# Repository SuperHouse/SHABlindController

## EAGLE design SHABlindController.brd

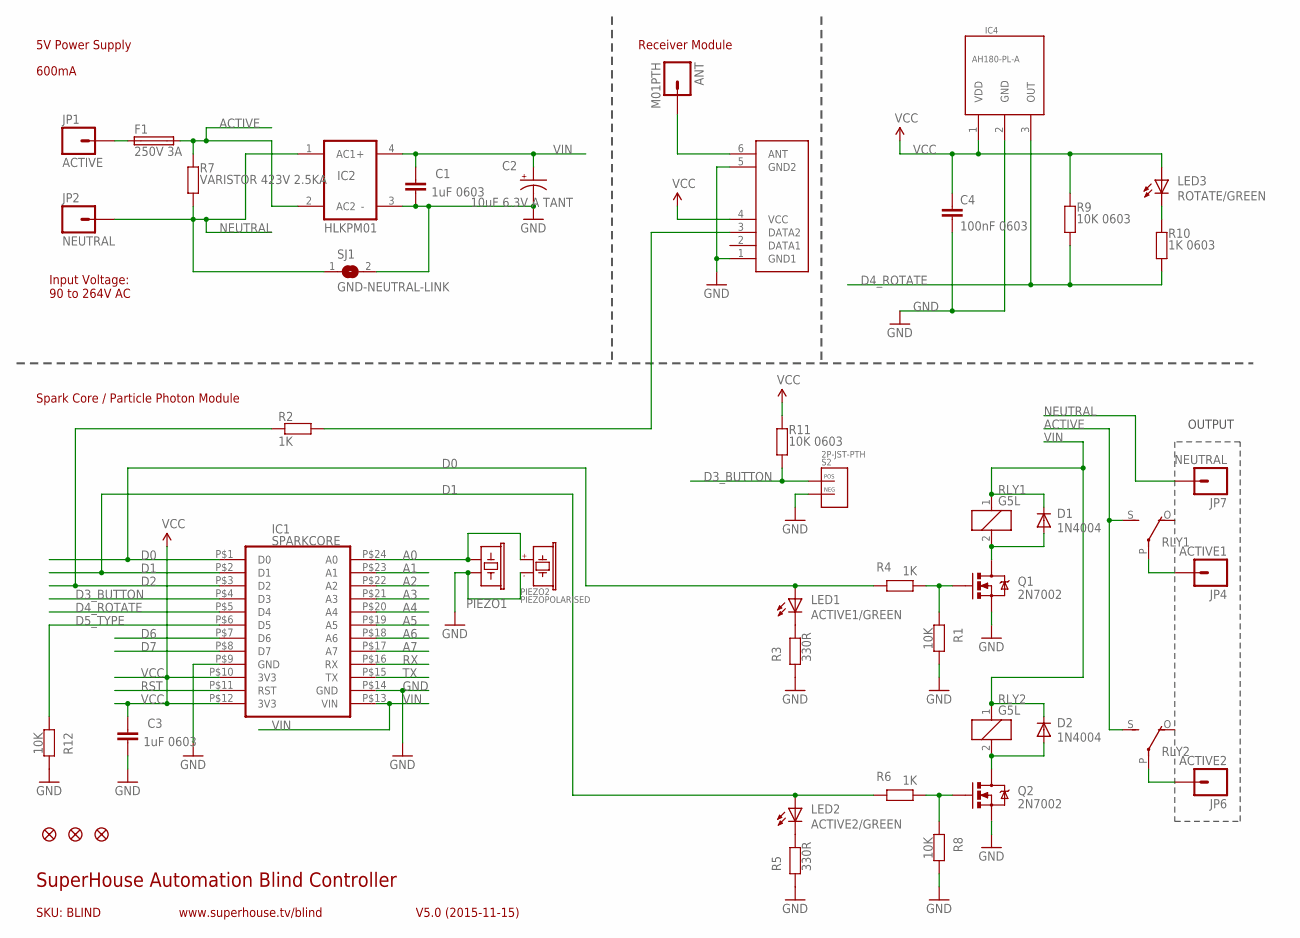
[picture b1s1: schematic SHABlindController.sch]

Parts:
ANT: M01PTH; 1X01
C1, C3: 1uF 0603; 0603@1
C2: 10uF 6.3V A TANT; EIA3216
C4: 100nF 0603; 0603
D1, D2: 1N4004; SMB-DIODE
F1: 250V 3A; PICOFUSE
FID1, FID2, FID3: FIDUCIAL1X2.5; FIDUCIAL-1X2.5
IC1: SPARKCORE
IC2: HLKPM01
IC3: RXB1; RX-B1-SHORT-FLAT
IC4: AH180-PL-A; TO92FLATUP
JP1: ACTIVE; 1X01LARGE
JP2, JP7: NEUTRAL; 1X01LARGE
JP4: ACTIVE1; 1X01LARGE
JP6: ACTIVE2; 1X01LARGE
LED1: ACTIVE1/GREEN; LED-0603
LED2: ACTIVE2/GREEN; LED-0603
LED3: ROTATE/GREEN; LED-0603
PIEZO1: BUZZERSMD12X12; BUZZER-12X12-SMT
PIEZO2: PIEZOPOLARISED; PIEZO12MMWIDEPOLARISED
Q1, Q2: 2N7002; SOT23-3
R1, R8, R12: 10K; 0603
R2, R4, R6: 1K; 0603
R3, R5: 330R; 0603
R7: VARISTOR 423V 2.5KA; AXIAL-0.3
R9, R11: 10K 0603; 0603
R10: 1K 0603; 0603
RLY1, RLY2: G5L; G5LE
S2: 2P-JST-PTH; JST-2MM-TH-RA
SJ1: GND-NEUTRAL-LINK; SJ

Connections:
A0: IC1.P$24 (A0), PIEZO1.1, PIEZO2.1 (+)
A1: IC1.P$23 (A1)
A2: IC1.P$22 (A2)
A3: IC1.P$21 (A3)
A4: IC1.P$20 (A4)
A5: IC1.P$19 (A5)
A6: IC1.P$18 (A6)
A7: IC1.P$17 (A7)
ACTIVE: F1.2, IC2.2 (AC2), R7.P$2 (2), RLY1.S, RLY2.S
D0: IC1.P$1 (D0), LED1.A, R4.2
D1: IC1.P$2 (D1), LED2.A, R6.2
D2: IC1.P$3 (D2), R2.1
D3_BUTTON: IC1.P$4 (D3), R11.1, S2.POS
D4_ROTATE: IC1.P$5 (D4), IC4.3 (OUT), R9.1, R10.2
D5_TYPE: IC1.P$6 (D5), R12.1
D6: IC1.P$7 (D6)
D7: IC1.P$8 (D7)
GND: C1.2, C2.C (-), C3.2, C4.2, IC1.P$9 (GND), IC1.P$14 (GND), IC2.3 (-), IC3.1 (GND1), IC3.5 (GND2), IC4.2 (GND), PIEZO1.2, PIEZO2.2 (-), Q1.2 (S), Q2.2 (S), R1.2, R3.1, R5.1, R8.2, R12.2, S2.NEG, SJ1.2
unnamed: ANT.1, IC3.6 (ANT)
unnamed: LED2.C, R5.2
unnamed: D2.A, Q2.3 (D), RLY2.2
unnamed: D1.A, Q1.3 (D), RLY1.2
unnamed: Q1.1 (G), R1.1, R4.1
unnamed: Q2.1 (G), R6.1, R8.1
unnamed: F1.1, JP1.1
unnamed: LED3.C, R10.1
unnamed: JP4.1, RLY1.P
unnamed: JP6.1, RLY2.P
unnamed: LED1.C, R3.2
unnamed: IC3.3 (DATA2), R2.2
NEUTRAL: IC2.1 (AC1), JP2.1, JP7.1, R7.P$1 (1), SJ1.1
RST: IC1.P$11 (RST)
RX: IC1.P$16 (RX)
TX: IC1.P$15 (TX)
VCC: C3.1, C4.1, IC1.P$10 (3V3), IC1.P$12 (3V3), IC3.4 (VCC), IC4.1 (VDD), LED3.A, R9.2, R11.2
VIN: C1.1, C2.A (+), D1.C, D2.C, IC1.P$13 (VIN), IC2.4 (+), RLY1.1, RLY2.1

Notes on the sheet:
SKU: BLIND
5V Power Supply
Spark Core / Particle Photon Module
600mA
SuperHouse Automation Blind Controller
V5.0 (2015-11-15)
www.superhouse.tv/blind
Receiver Module
OUTPUT
Input Voltage: 90 to 264V AC

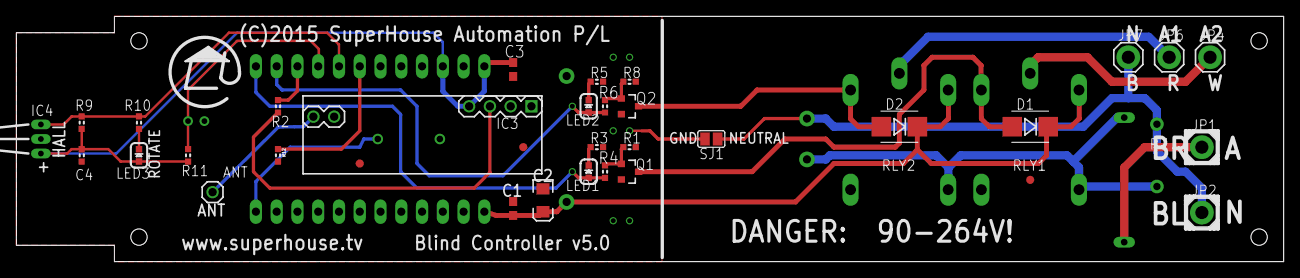
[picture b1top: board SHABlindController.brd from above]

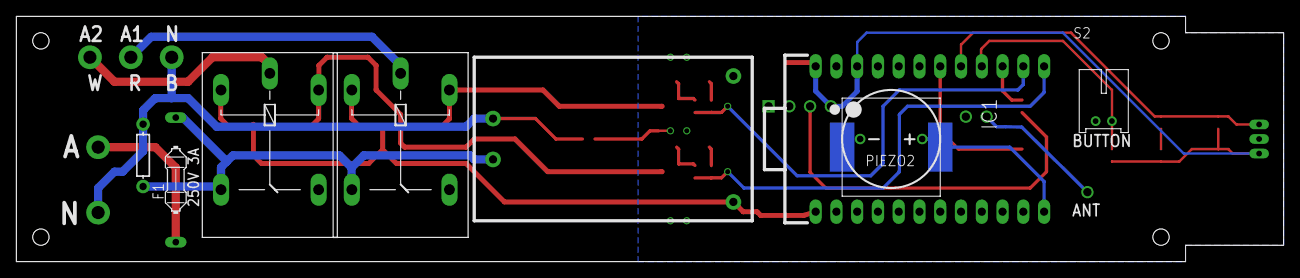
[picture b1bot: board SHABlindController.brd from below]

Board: 2 copper layers, 155.0 x 30.0 mm, 43 parts (9 on the bottom side), 24 nets.

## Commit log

2014-05-07 v1.0 release
2014-06-13 Reshaped board to fit blind mounts
2014-08-31 Replaced MCU and XBee with Spark Core
2014-11-16 Improved routing for v2.0 release
2014-11-16 Changed power supply from 3.3V to 5V
2014-11-18 Replaced TRIACs with relays; changed power supply to 5V; added piezo
2015-05-25 Release v3.0
2015-07-07 v4.0 release: improved 433MHz rx footprint, added PTH option for piezo
2015-07-07 Added v3.0 production files
2015-07-08 v4.1 release: Added fuse mount; added Molex 15-24-4441 (8981 series) connector
2015-07-08 Added value to fuse
2015-11-09 Added solder-jumper to link GND and Neutral Reduced spacing between relays Increased length of fuse footprint
2018-01-23 Layout updates

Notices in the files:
SHABlindController.brd:
(C)2015 SuperHouse Automation P/L
